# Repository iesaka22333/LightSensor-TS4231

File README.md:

# LightSensor-TS4231
A versatile optical sensing module built around the TS4231 chip. It supports two primary use cases: acting as a receiver for Lighthouse (SteamVR) tracking systems, or functioning as a standalone high-speed photodiode sensor. Its low-latency response and modular design make it suitable for applications in motion tracking, light signal analysis, and embedded optical systems.

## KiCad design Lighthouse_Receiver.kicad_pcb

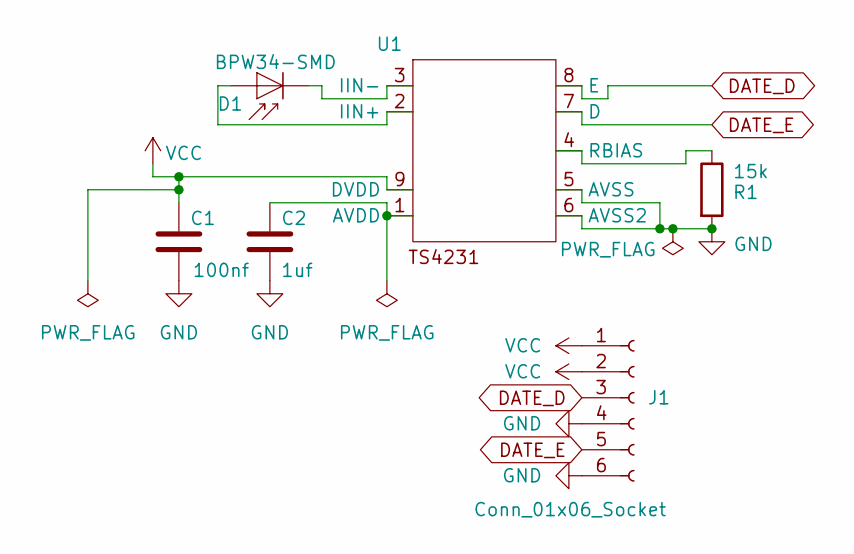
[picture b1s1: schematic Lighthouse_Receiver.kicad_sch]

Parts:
C1: 100nf; C_0402_1005Metric
C2: 1uf; C_0402_1005Metric
D1: BPW34-SMD; Osram_BPW34S-SMD
J1: Conn_01x06_Socket; Hirose_FH12-6S-0.5SH_1x06-1MP_P0.50mm_Horizontal
R1: 15k; C_0402_1005Metric
U1: WLCSP-9_3x3_B1.66x1.66mm_P0.5mm

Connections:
DATE_D: J1.3, U1.8 (E)
DATE_E: J1.5, U1.7 (D)
GND: C1.2, C2.2, J1.4, J1.6, R1.2, U1.5 (AVSS), U1.6 (AVSS2)
unnamed: D1.2 (A), U1.2 (IIN+)
unnamed: D1.1 (K), U1.3 (IIN-)
unnamed: C2.1, U1.1 (AVDD)
unnamed: R1.1, U1.4 (RBIAS)
VCC: C1.1, J1.1, J1.2, U1.9 (DVDD)

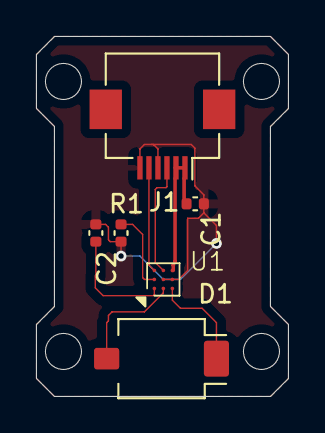
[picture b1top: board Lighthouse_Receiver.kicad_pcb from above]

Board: 2 copper layers, 14.0 x 20.0 mm, 6 parts (0 on the bottom side), 8 nets.

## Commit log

2025-04-11 Add files via upload
    v1.0
